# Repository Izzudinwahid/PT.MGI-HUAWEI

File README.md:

# PT.MGI-HUAWEI
PCB Main dan Konektor

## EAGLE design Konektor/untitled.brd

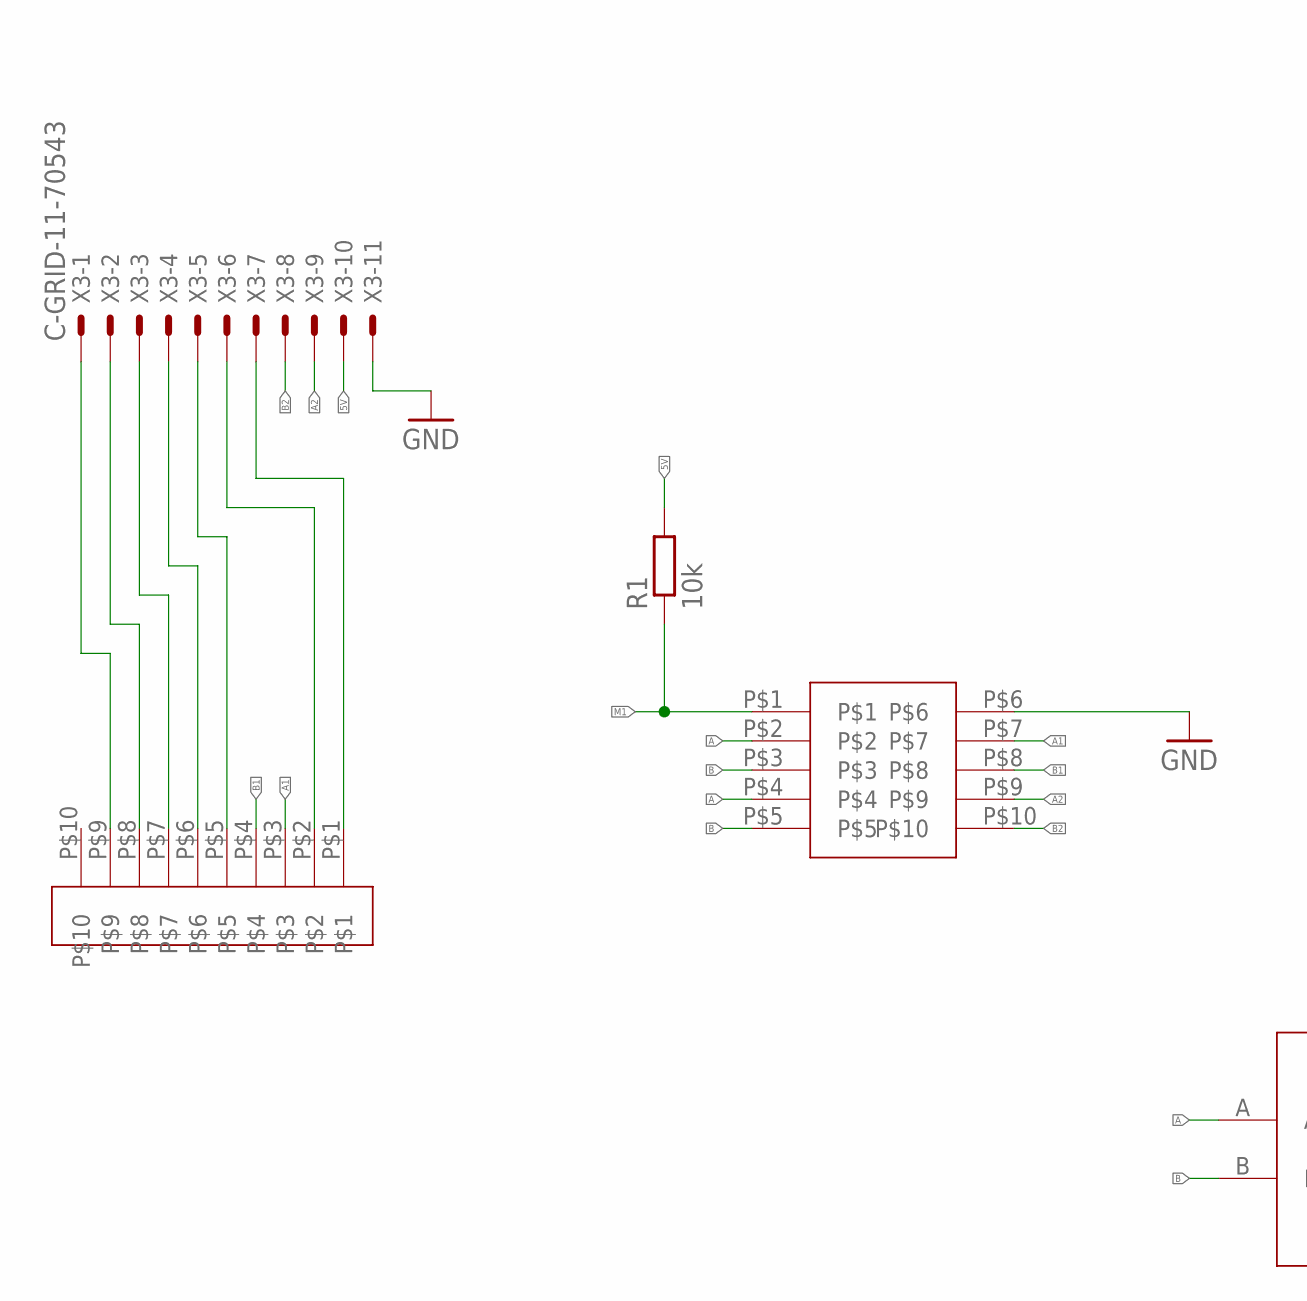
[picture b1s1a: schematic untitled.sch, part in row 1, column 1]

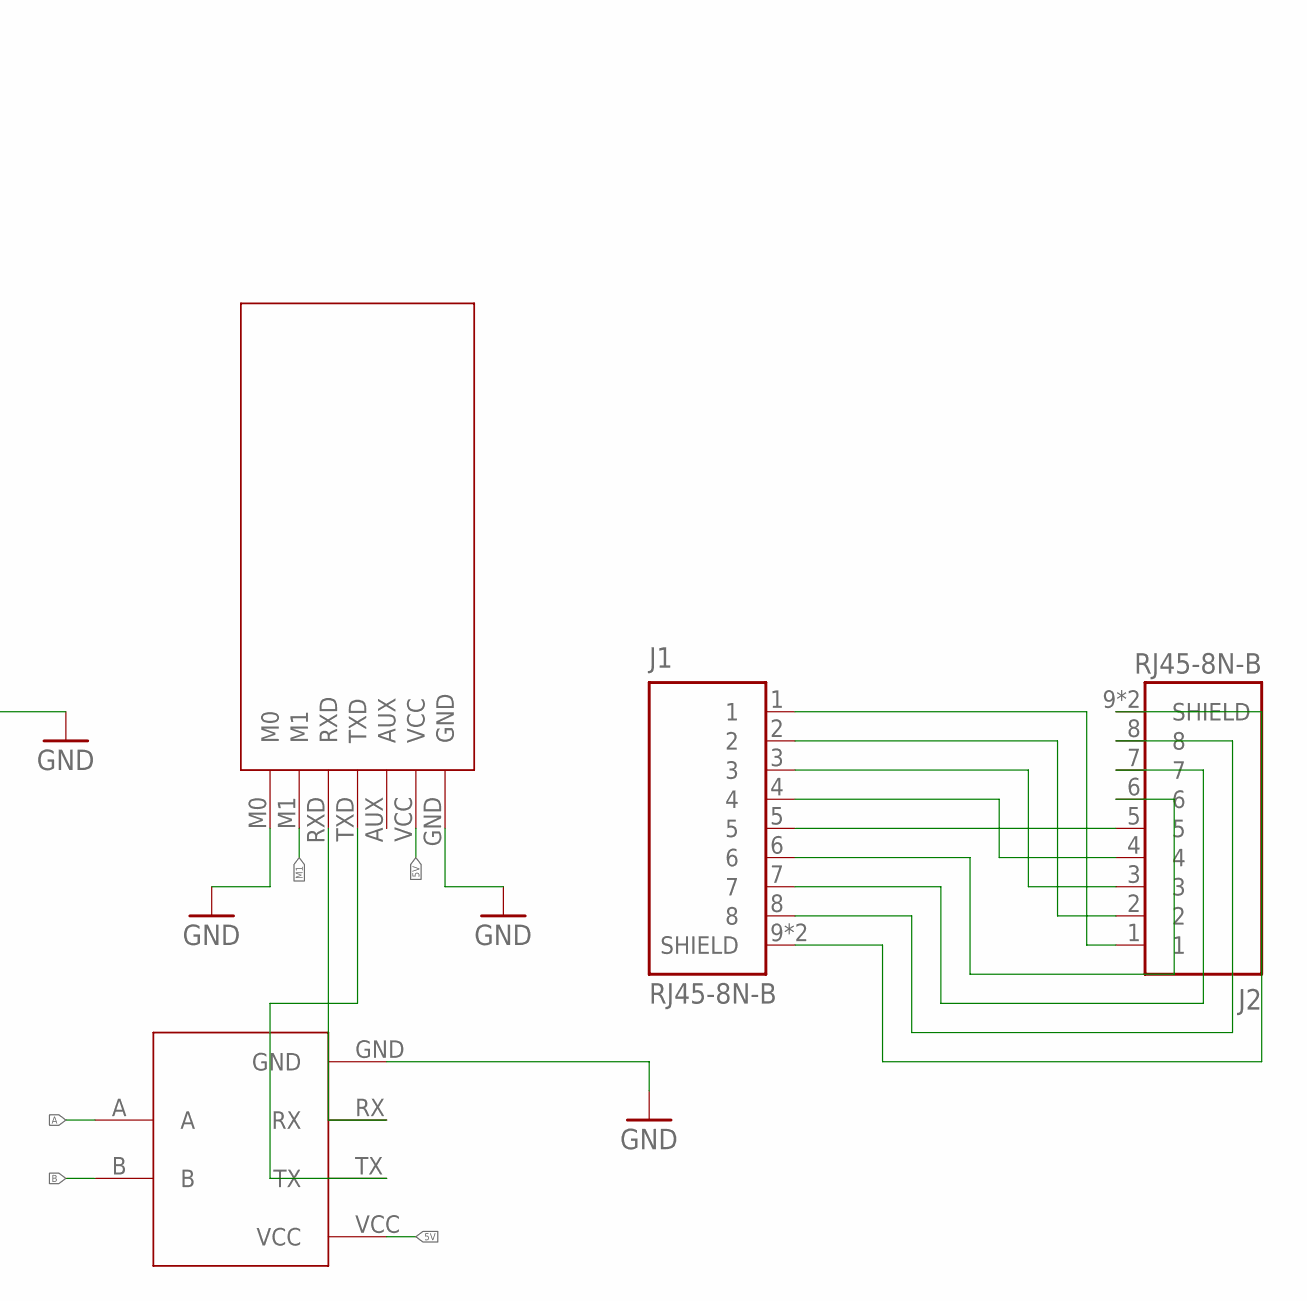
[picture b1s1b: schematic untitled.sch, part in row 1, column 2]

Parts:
DP-05RP1: DP-05RP
EBYTEE220-900T22D1: EBYTEE220-900T22D
J1, J2: RJ45-8N-B; TE_RJ45-8N-B
KONEKTOR-3.81-13P1: KONEKTOR-3.81-13P
R1: 10k; R0805
TTL-RS1: TTL-RS485
X3: C-GRID-11-70543; 70543-11

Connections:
5V: EBYTEE220-900T22D1.VCC, R1.2, TTL-RS1.VCC, X3.10
A: DP-05RP1.P$2, DP-05RP1.P$4, TTL-RS1.A
A1: DP-05RP1.P$7, KONEKTOR-3.81-13P1.P$3
A2: DP-05RP1.P$9, X3.9
B: DP-05RP1.P$3, DP-05RP1.P$5, TTL-RS1.B
B1: DP-05RP1.P$8, KONEKTOR-3.81-13P1.P$4
B2: DP-05RP1.P$10, X3.8
GND: DP-05RP1.P$6, EBYTEE220-900T22D1.GND, EBYTEE220-900T22D1.M0, TTL-RS1.GND, X3.11
M1: DP-05RP1.P$1, EBYTEE220-900T22D1.M1, R1.1
unnamed: KONEKTOR-3.81-13P1.P$1, X3.7
unnamed: KONEKTOR-3.81-13P1.P$2, X3.6
unnamed: EBYTEE220-900T22D1.RXD, TTL-RS1.RX
unnamed: EBYTEE220-900T22D1.TXD, TTL-RS1.TX
unnamed: KONEKTOR-3.81-13P1.P$5, X3.5
unnamed: J1.1, J2.1
unnamed: J1.2, J2.2
unnamed: J1.3, J2.3
unnamed: J1.4, J2.4
unnamed: J1.5, J2.5
unnamed: J1.6, J2.6
unnamed: J1.7, J2.7
unnamed: KONEKTOR-3.81-13P1.P$6, X3.4
unnamed: KONEKTOR-3.81-13P1.P$7, X3.3
unnamed: KONEKTOR-3.81-13P1.P$8, X3.2
unnamed: KONEKTOR-3.81-13P1.P$9, X3.1
unnamed: J1.8, J2.8
unnamed: J1.9 (SHIELD), J1.10 (SHIELD), J2.9 (SHIELD), J2.10 (SHIELD)

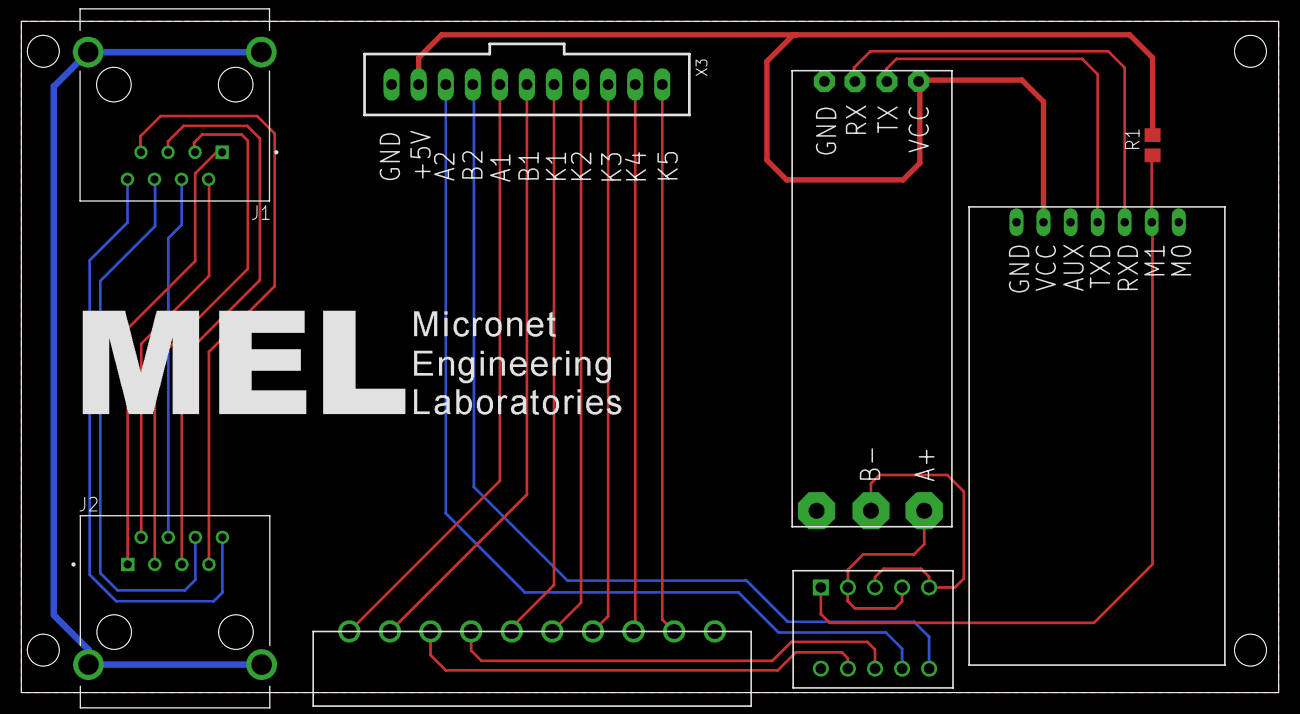
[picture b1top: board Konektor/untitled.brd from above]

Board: 2 copper layers, 118.0 x 63.0 mm, 8 parts (0 on the bottom side), 27 nets.

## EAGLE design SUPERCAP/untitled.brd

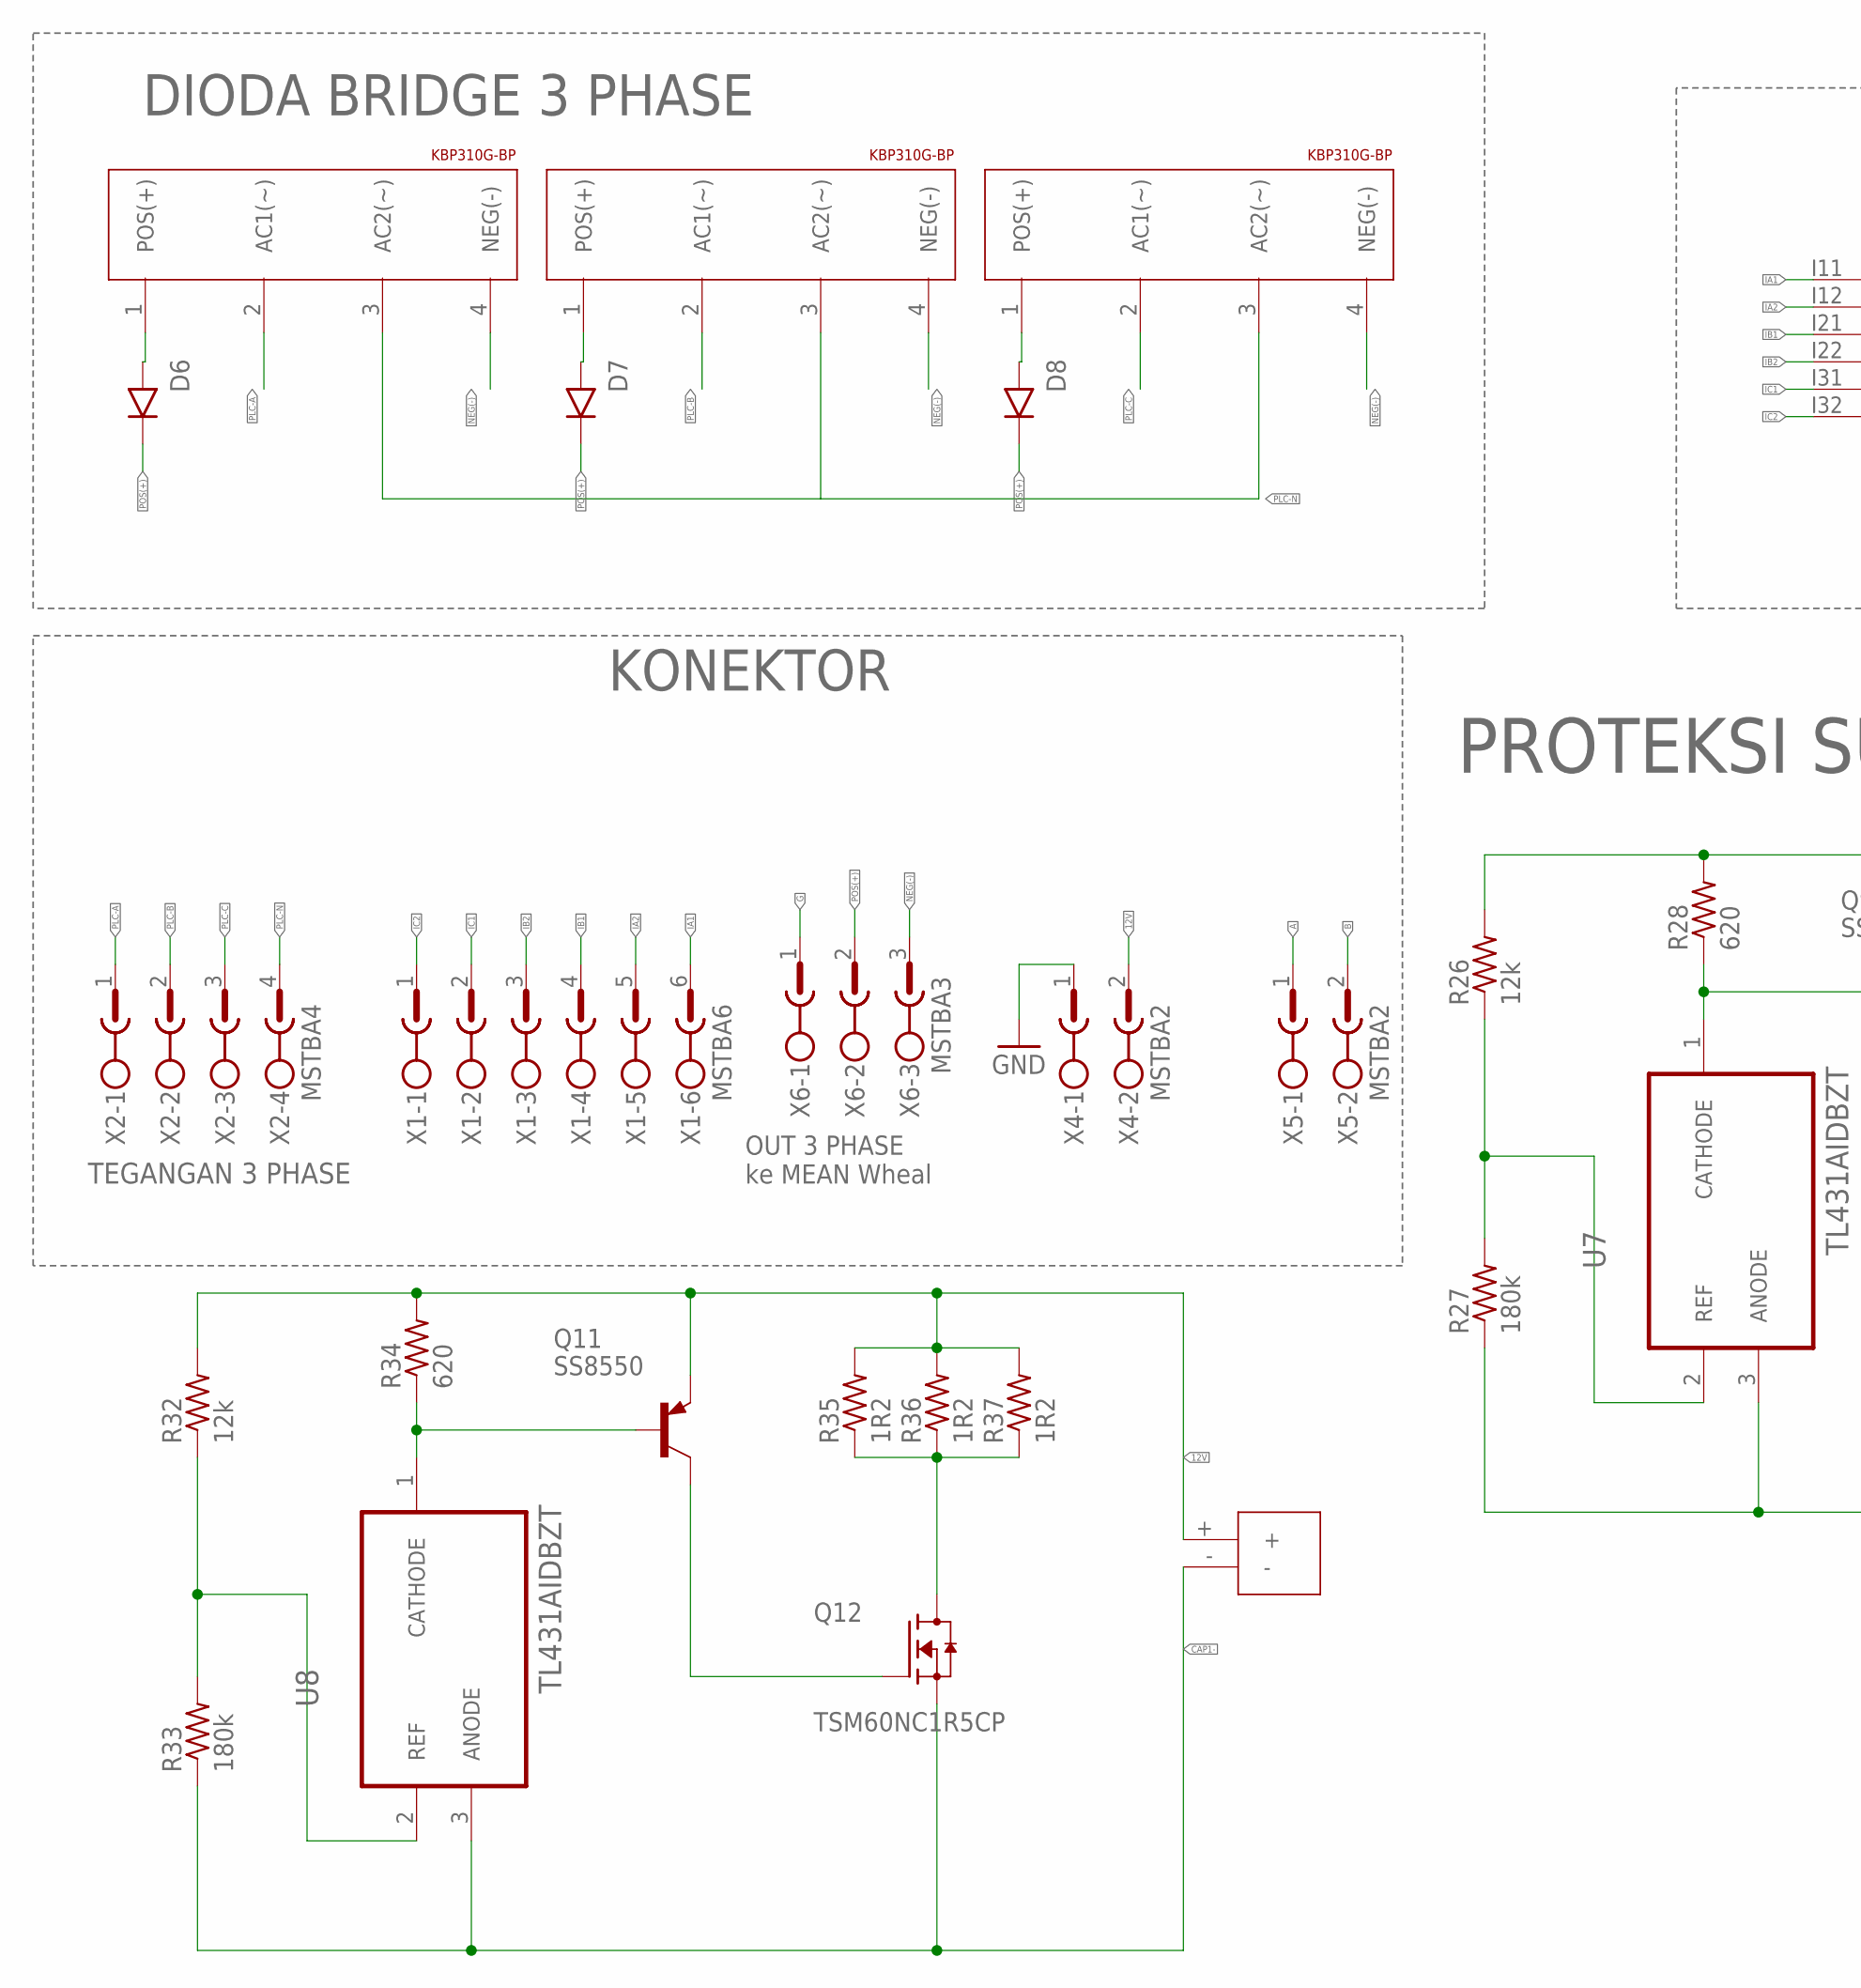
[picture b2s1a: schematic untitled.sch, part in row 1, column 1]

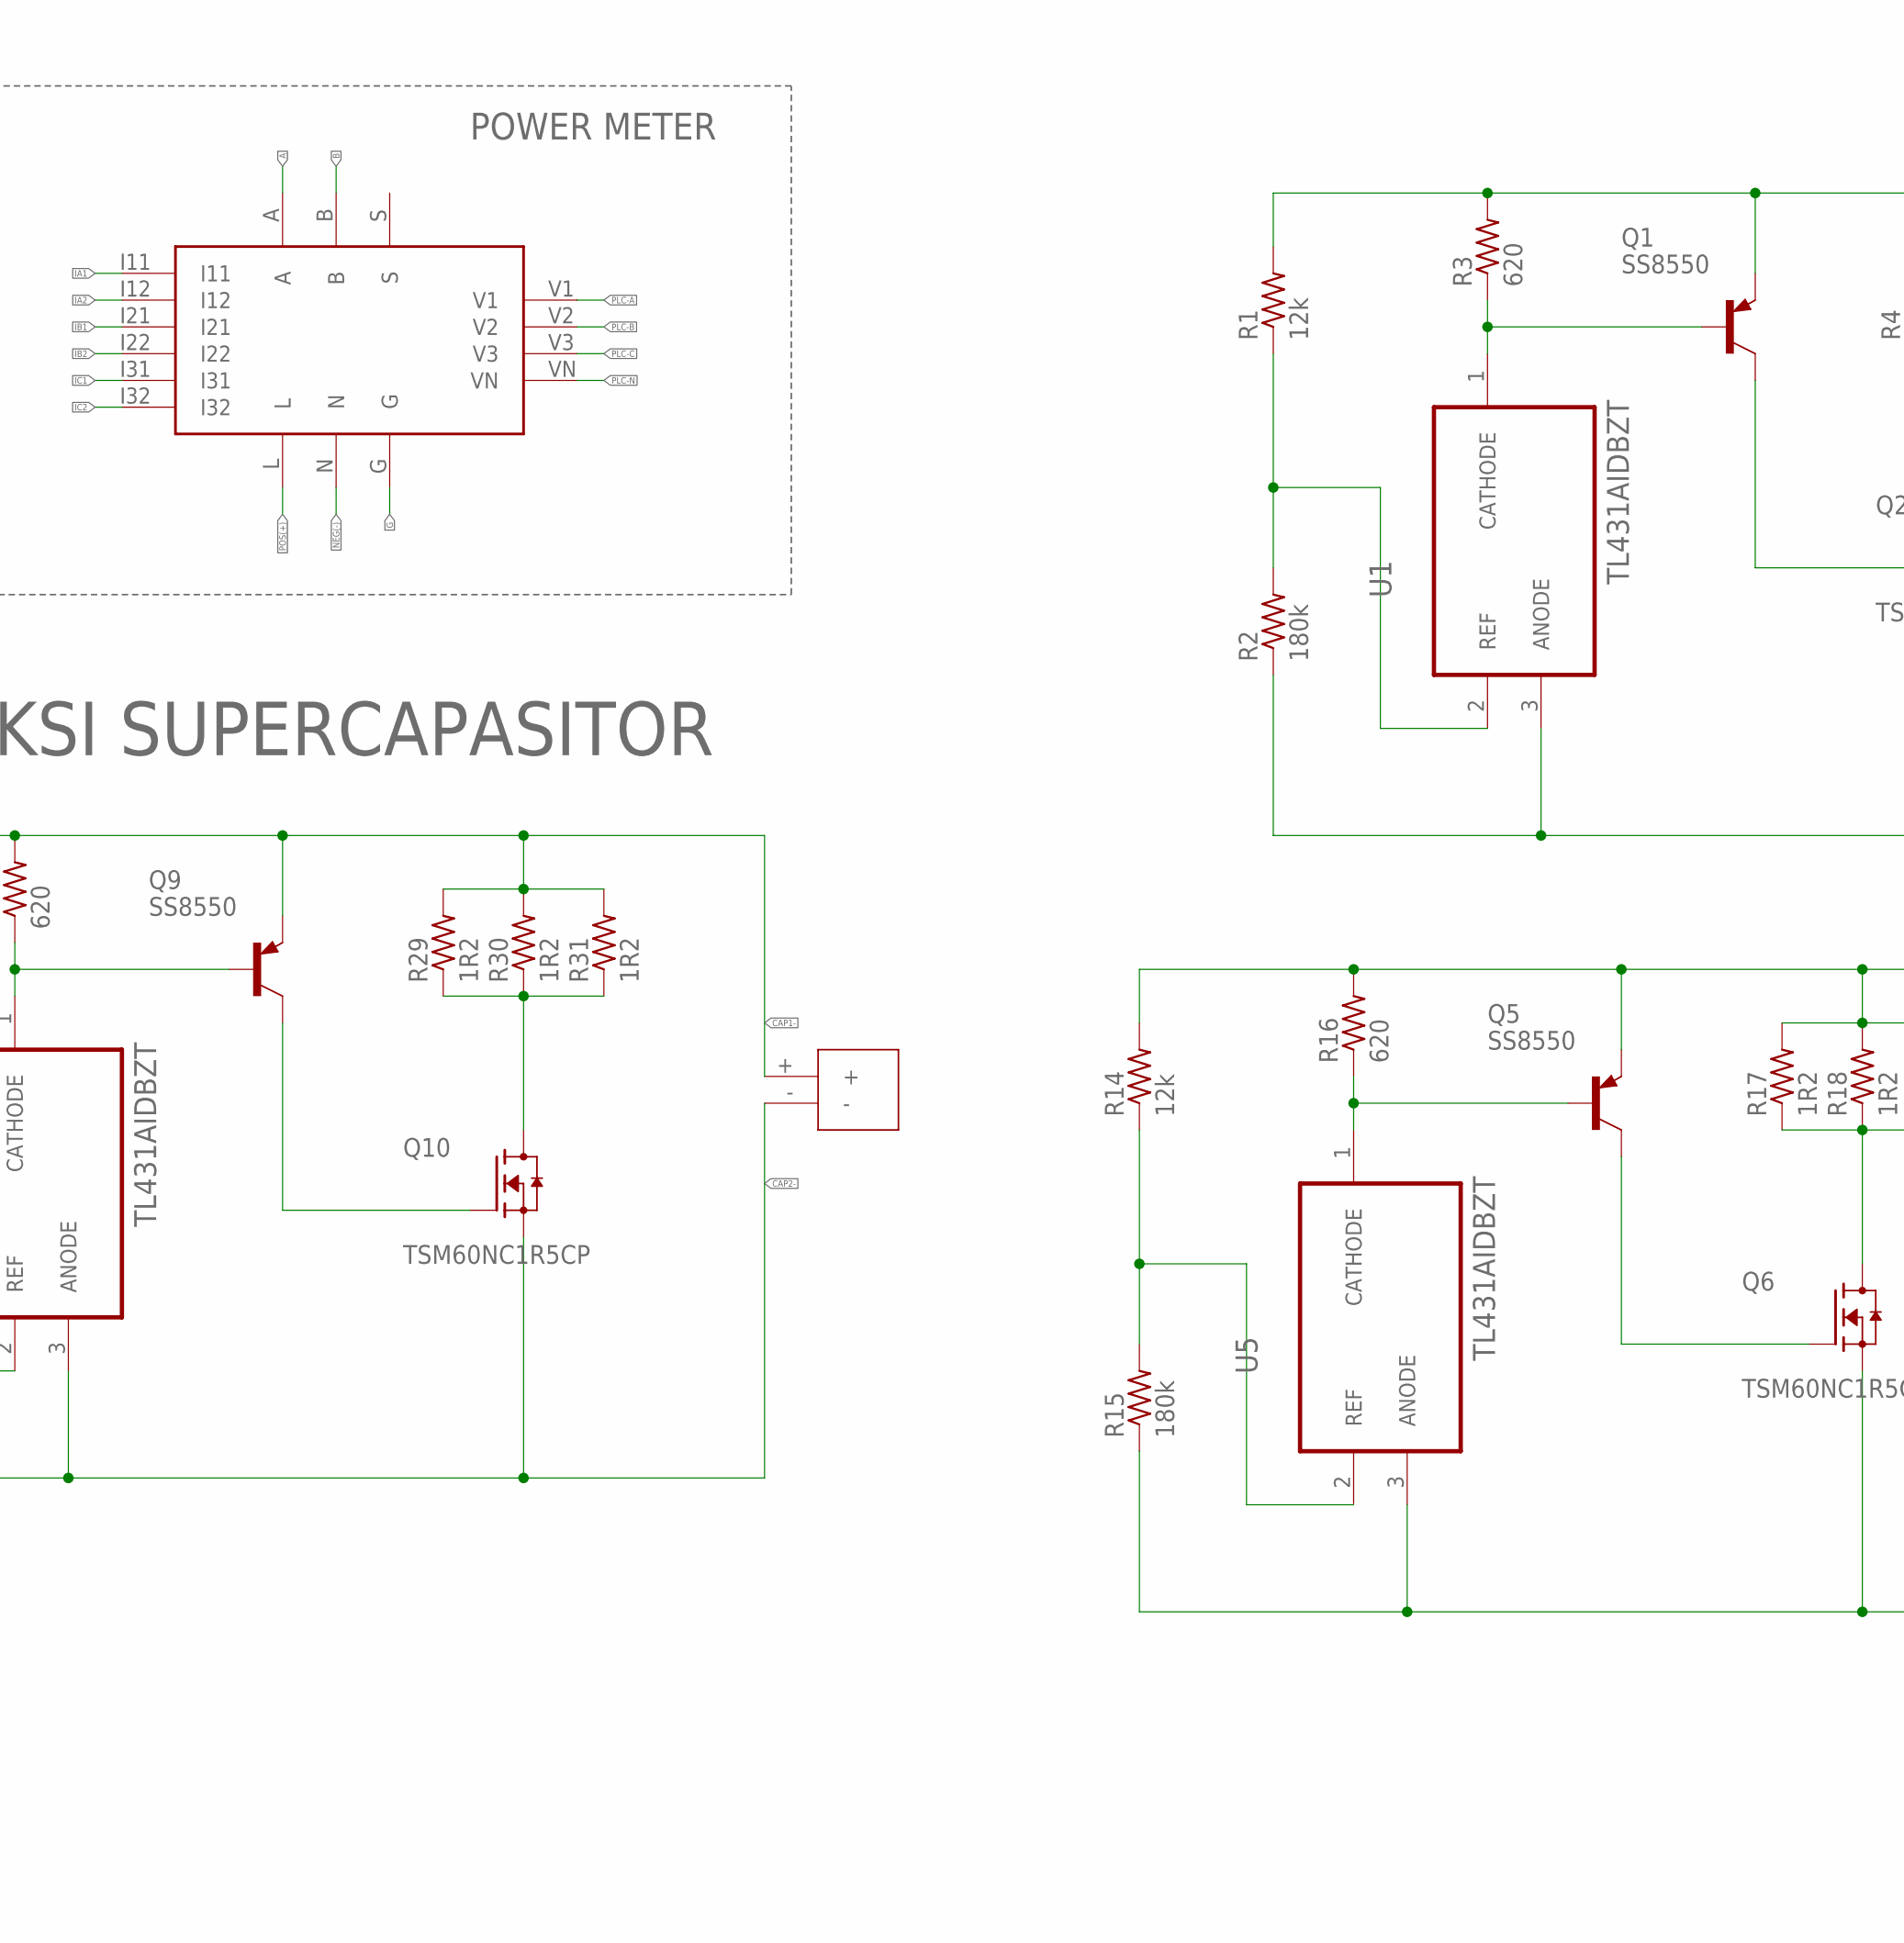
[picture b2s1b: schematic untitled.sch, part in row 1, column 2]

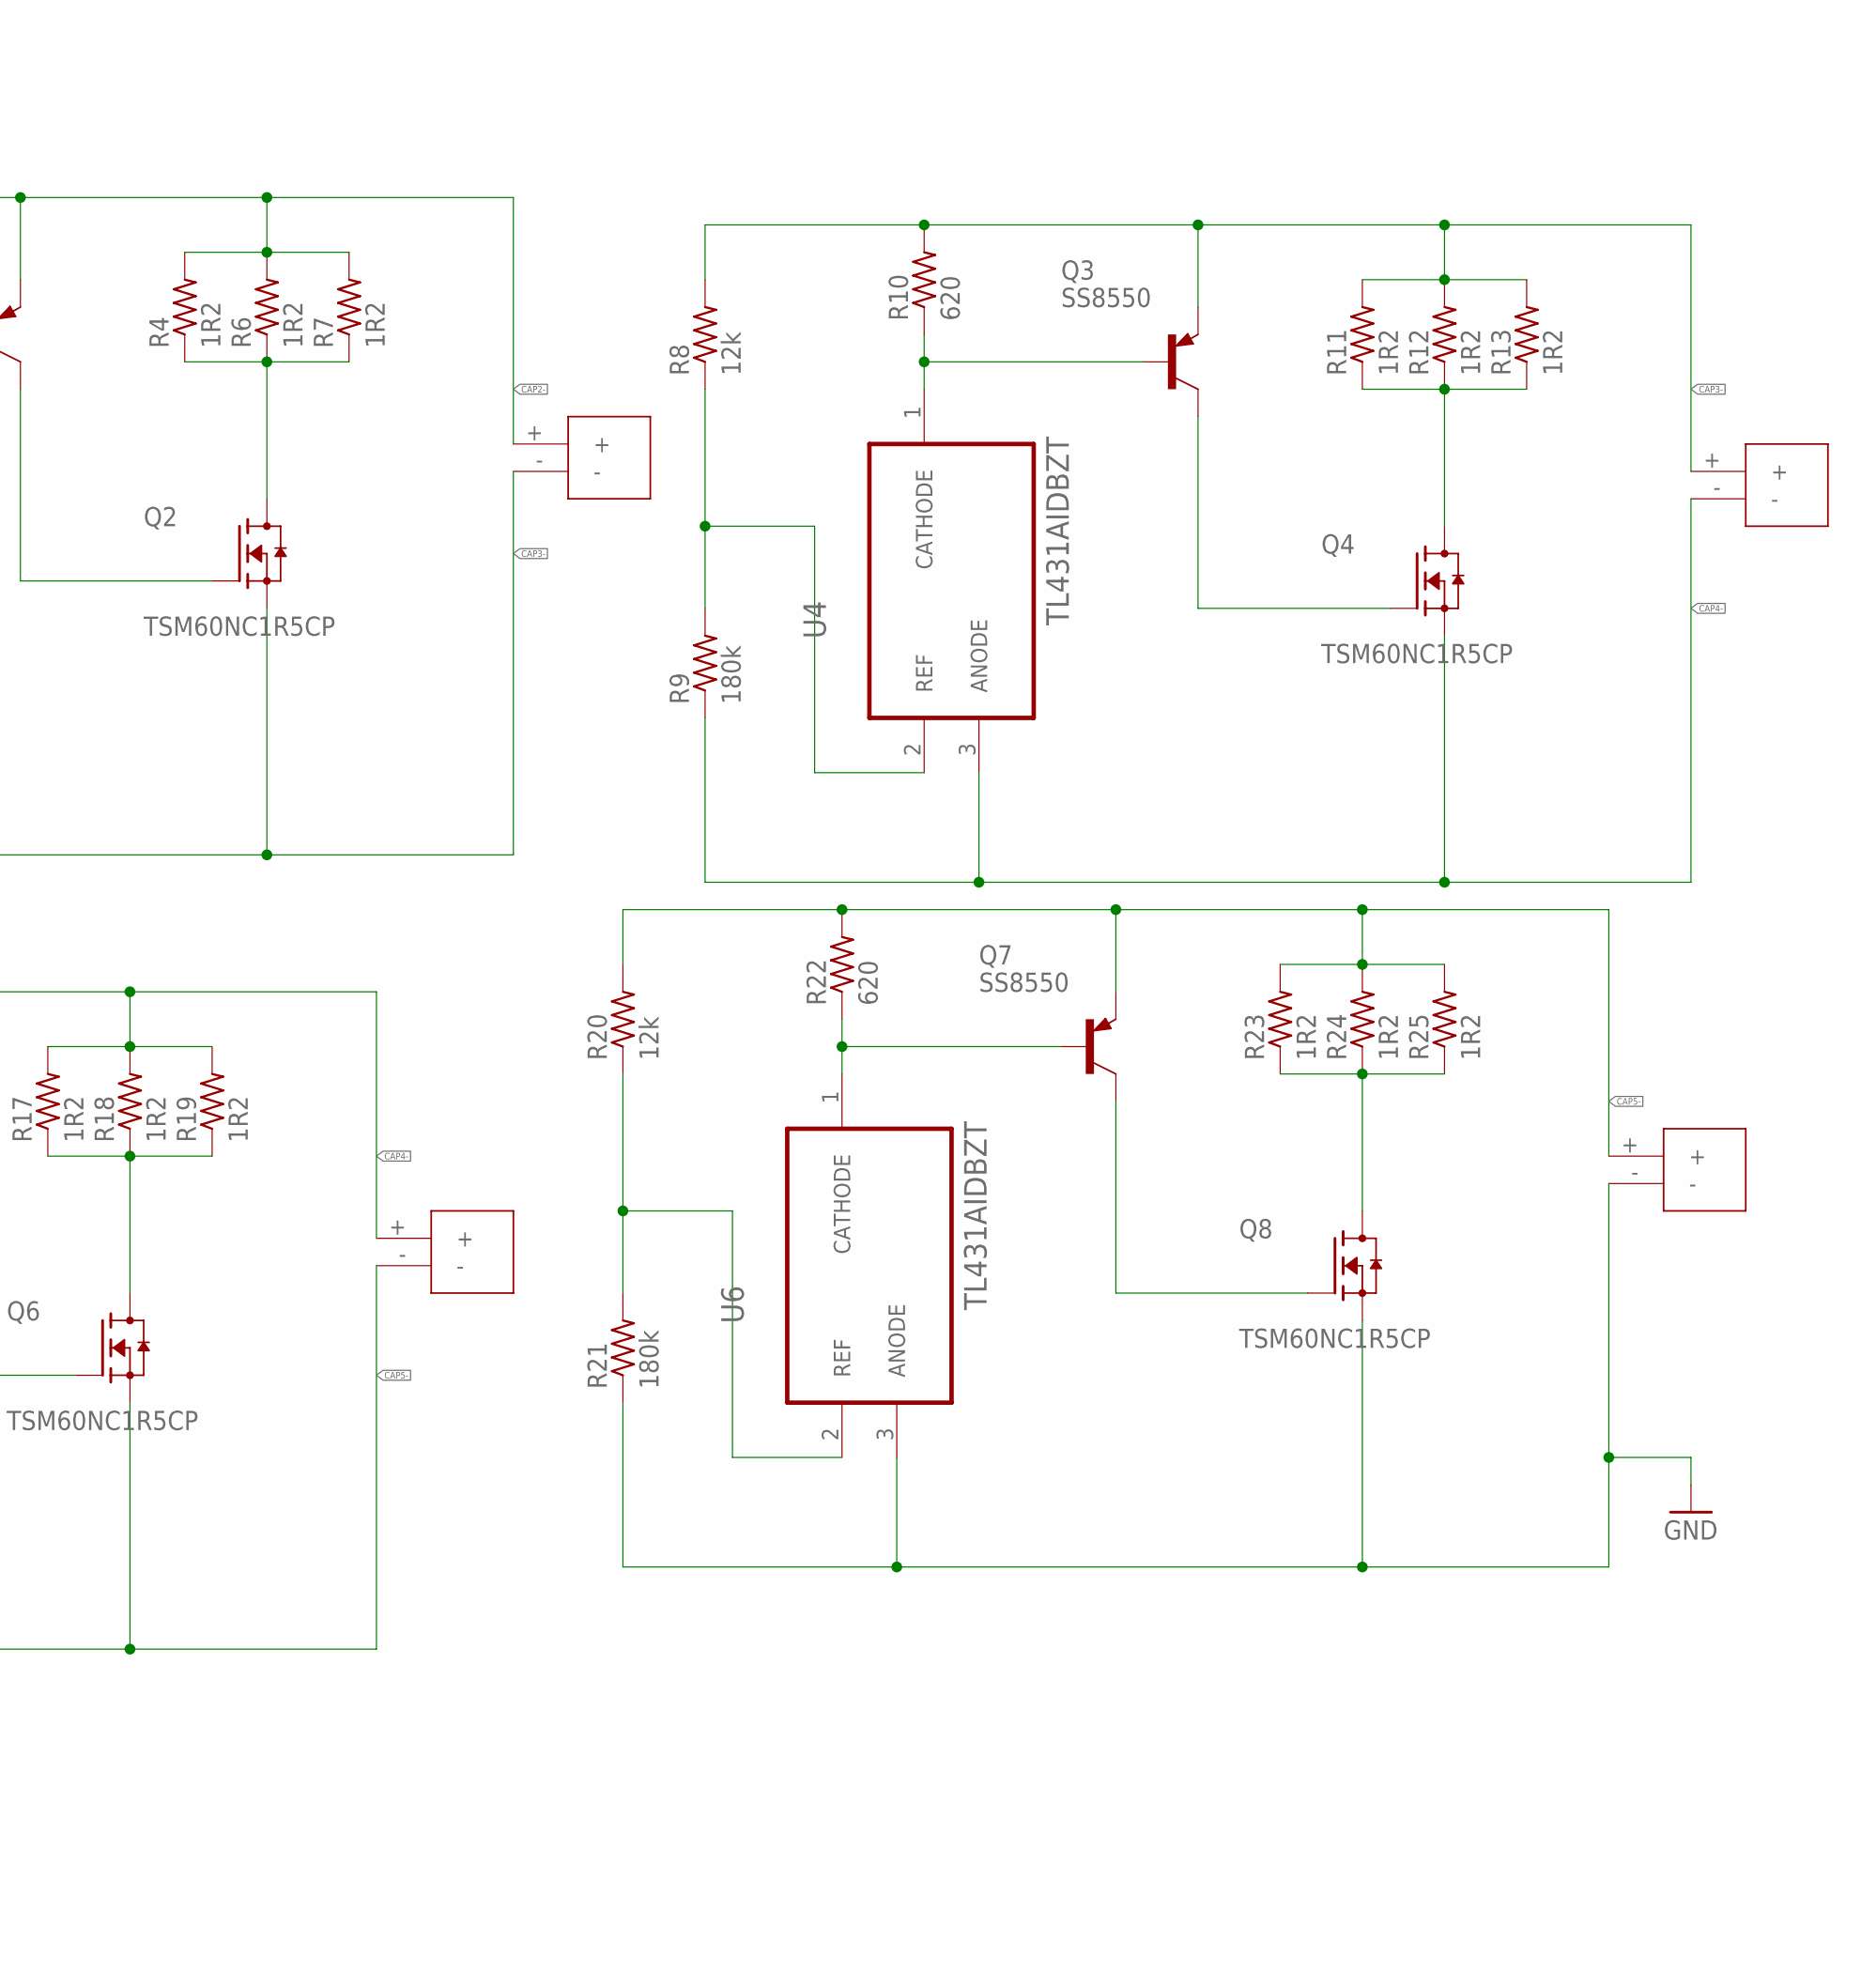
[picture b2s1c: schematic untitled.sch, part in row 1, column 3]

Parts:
D6, D7, D8: 1N4001; DO41-10
POWERMETER1: POWERMETER
Q1, Q3, Q5, Q7, Q9, Q11: SS8550; SOT-23_BEC
Q2, Q4, Q6, Q8, Q10, Q12: TSM60NC1R5CP; TRANS_TSM60NC1R5CP
R1, R8, R14, R20, R26, R32: 12k; R0805
R2, R9, R15, R21, R27, R33: 180k; R0805
R3, R10, R16, R22, R28, R34: 620; R0805
R4, R6, R7, R11, R12, R13, R17, R18, R19, R23, R24, R25, R29, R30, R31, R35, R36, R37: 1R2; R2512
SUPERCAP1, SUPERCAP2, SUPERCAP3, SUPERCAP4, SUPERCAP5, SUPERCAP6: 2.7/500F; SUPERCAP
U1, U4, U5, U6, U7, U8: TL431AIDBZT; SOT95P237X112-3N
U$1, U$2, U$3: KBP310G-BP
X1: MSTBA6
X2: MSTBA4
X4, X5: MSTBA2
X6: MSTBA3

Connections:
12V: Q11.E, R32.2, R34.2, R35.2, R36.2, R37.2, SUPERCAP6.+, X4.2
A: POWERMETER1.A, X5.1
B: POWERMETER1.B, X5.2
CAP1-: Q9.E, Q12.3 (S), R26.2, R28.2, R29.2, R30.2, R31.2, R33.1, SUPERCAP5.+, SUPERCAP6.-, U8.3 (ANODE)
CAP2-: Q1.E, Q10.3 (S), R1.2, R3.2, R4.2, R6.2, R7.2, R27.1, SUPERCAP1.+, SUPERCAP5.-, U7.3 (ANODE)
CAP3-: Q2.3 (S), Q3.E, R2.1, R8.2, R10.2, R11.2, R12.2, R13.2, SUPERCAP1.-, SUPERCAP2.+, U1.3 (ANODE)
CAP4-: Q4.3 (S), Q5.E, R9.1, R14.2, R16.2, R17.2, R18.2, R19.2, SUPERCAP2.-, SUPERCAP3.+, U4.3 (ANODE)
CAP5-: Q6.3 (S), Q7.E, R15.1, R20.2, R22.2, R23.2, R24.2, R25.2, SUPERCAP3.-, SUPERCAP4.+, U5.3 (ANODE)
G: POWERMETER1.G, X6.1
GND: Q8.3 (S), R21.1, SUPERCAP4.-, U6.3 (ANODE), X4.1
IA1: POWERMETER1.I11, X1.6
IA2: POWERMETER1.I12, X1.5
IB1: POWERMETER1.I21, X1.4
IB2: POWERMETER1.I22, X1.3
IC1: POWERMETER1.I31, X1.2
IC2: POWERMETER1.I32, X1.1
unnamed: D6.A (ANODE), U$1.1 (POS(+))
unnamed: D7.A (ANODE), U$2.1 (POS(+))
unnamed: D8.A (ANODE), U$3.1 (POS(+))
unnamed: R8.1, R9.2, U4.2 (REF)
unnamed: R1.1, R2.2, U1.2 (REF)
unnamed: Q1.B, R3.1, U1.1 (CATHODE)
unnamed: Q1.C, Q2.1 (G)
unnamed: Q2.2 (D), R4.1, R6.1, R7.1
unnamed: Q3.B, R10.1, U4.1 (CATHODE)
unnamed: Q3.C, Q4.1 (G)
unnamed: Q4.2 (D), R11.1, R12.1, R13.1
unnamed: R14.1, R15.2, U5.2 (REF)
unnamed: Q5.B, R16.1, U5.1 (CATHODE)
unnamed: Q5.C, Q6.1 (G)
unnamed: Q6.2 (D), R17.1, R18.1, R19.1
unnamed: R20.1, R21.2, U6.2 (REF)
unnamed: Q7.B, R22.1, U6.1 (CATHODE)
unnamed: Q7.C, Q8.1 (G)
unnamed: Q8.2 (D), R23.1, R24.1, R25.1
unnamed: R26.1, R27.2, U7.2 (REF)
unnamed: Q9.B, R28.1, U7.1 (CATHODE)
unnamed: Q9.C, Q10.1 (G)
unnamed: Q10.2 (D), R29.1, R30.1, R31.1
unnamed: R32.1, R33.2, U8.2 (REF)
unnamed: Q11.B, R34.1, U8.1 (CATHODE)
unnamed: Q11.C, Q12.1 (G)
unnamed: Q12.2 (D), R35.1, R36.1, R37.1
NEG(-): POWERMETER1.N, U$1.4 (NEG(-)), U$2.4 (NEG(-)), U$3.4 (NEG(-)), X6.3
PLC-A: POWERMETER1.V1, U$1.2 (AC1(~)), X2.1
PLC-B: POWERMETER1.V2, U$2.2 (AC1(~)), X2.2
PLC-C: POWERMETER1.V3, U$3.2 (AC1(~)), X2.3
PLC-N: POWERMETER1.VN, U$1.3 (AC2(~)), U$2.3 (AC2(~)), U$3.3 (AC2(~)), X2.4
POS(+): D6.C (CATHODE), D7.C (CATHODE), D8.C (CATHODE), POWERMETER1.L, X6.2

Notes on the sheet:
DIODA BRIDGE 3 PHASE
KONEKTOR
TEGANGAN 3 PHASE
OUT 3 PHASE ke MEAN Wheal
PROTEKSI SUPERCAPASITOR
POWER METER

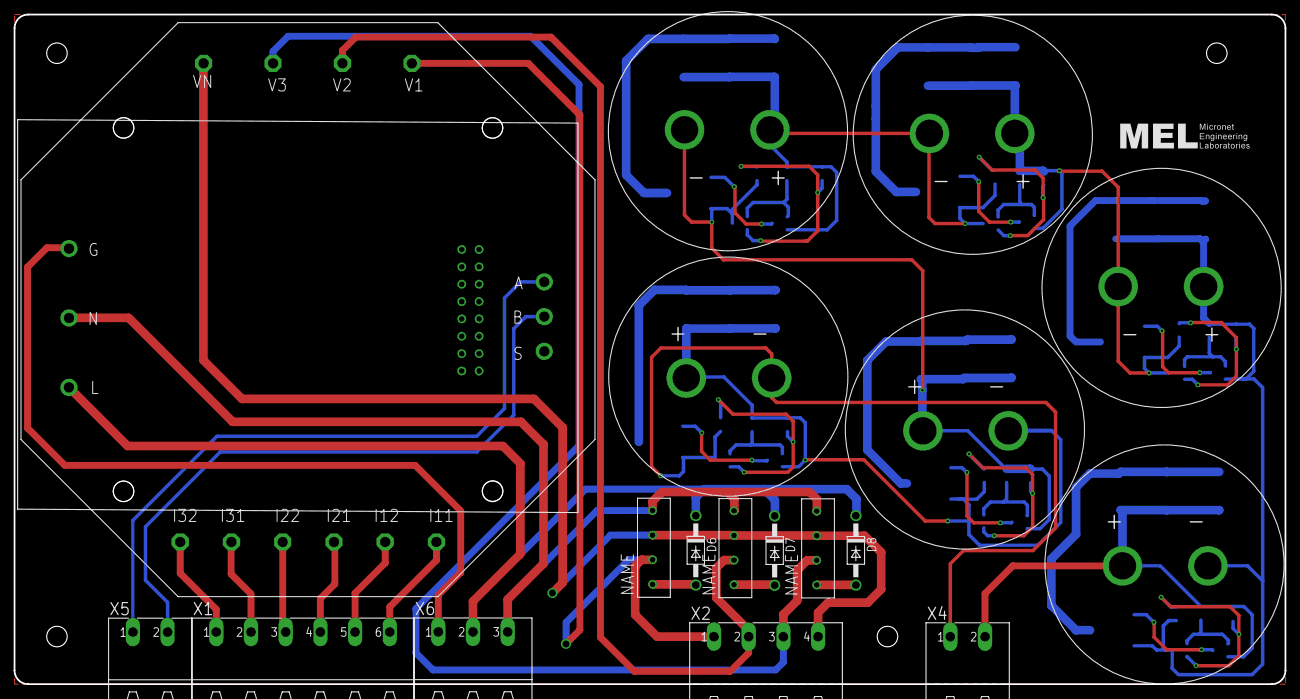
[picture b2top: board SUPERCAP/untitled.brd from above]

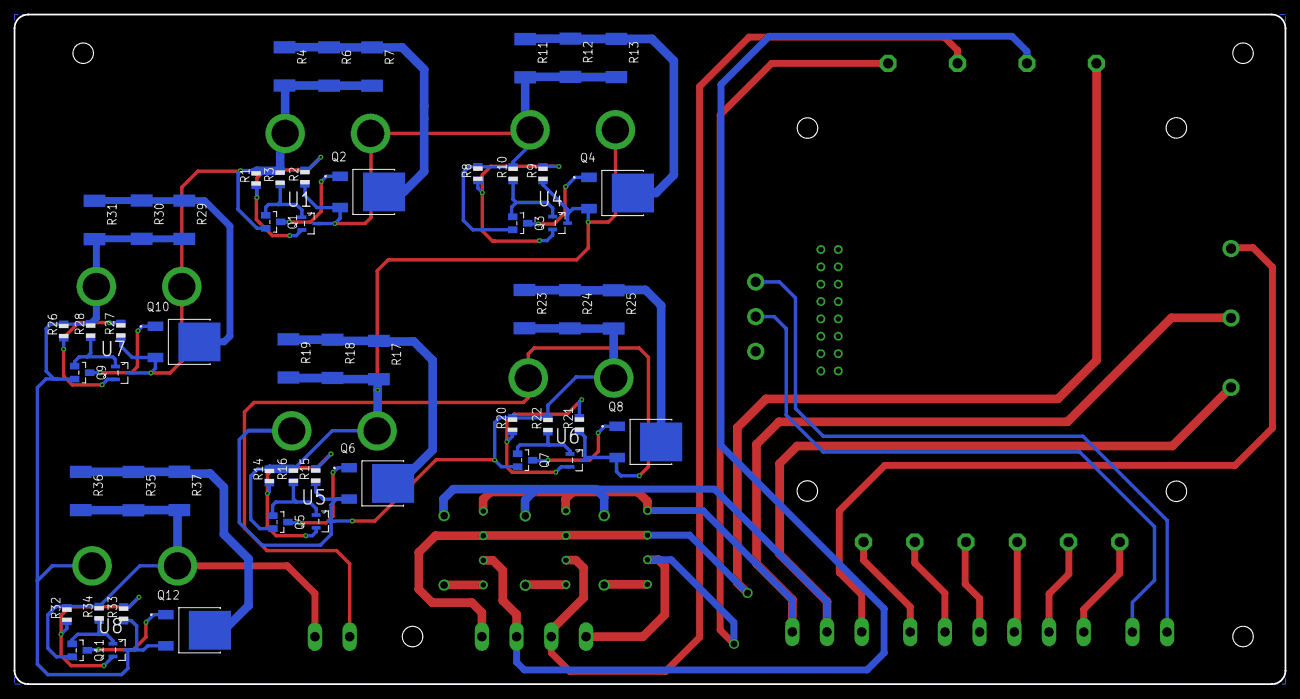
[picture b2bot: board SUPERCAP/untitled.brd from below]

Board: 2 copper layers, 186.0 x 98.0 mm, 72 parts (54 on the bottom side), 49 nets.
